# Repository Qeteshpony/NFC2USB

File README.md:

# NFC2USB

[Documentation](https://qeteshpony.github.io/NFC2USB)

Connect an RC522 based NFC-Reader to your computer using USB

The project is based around an [ESP32-S2FH4](https://www.espressif.com/sites/default/files/documentation/esp32-s2_datasheet_en.pdf) with it's most basic support components and no RF circuitry since we just need GPIO and processing power. It would have been possible to solve this with a much simpler microcontroller but availability and pricing at the time of development made the ESP32 with built in USB and flash the best choice. 

The board is designed using KiCAD 6 with production and assembly by JLCPCB in mind. All parts are selected to be available from JLCPCB at the time of writing and as many parts as possible are used from their basic library.

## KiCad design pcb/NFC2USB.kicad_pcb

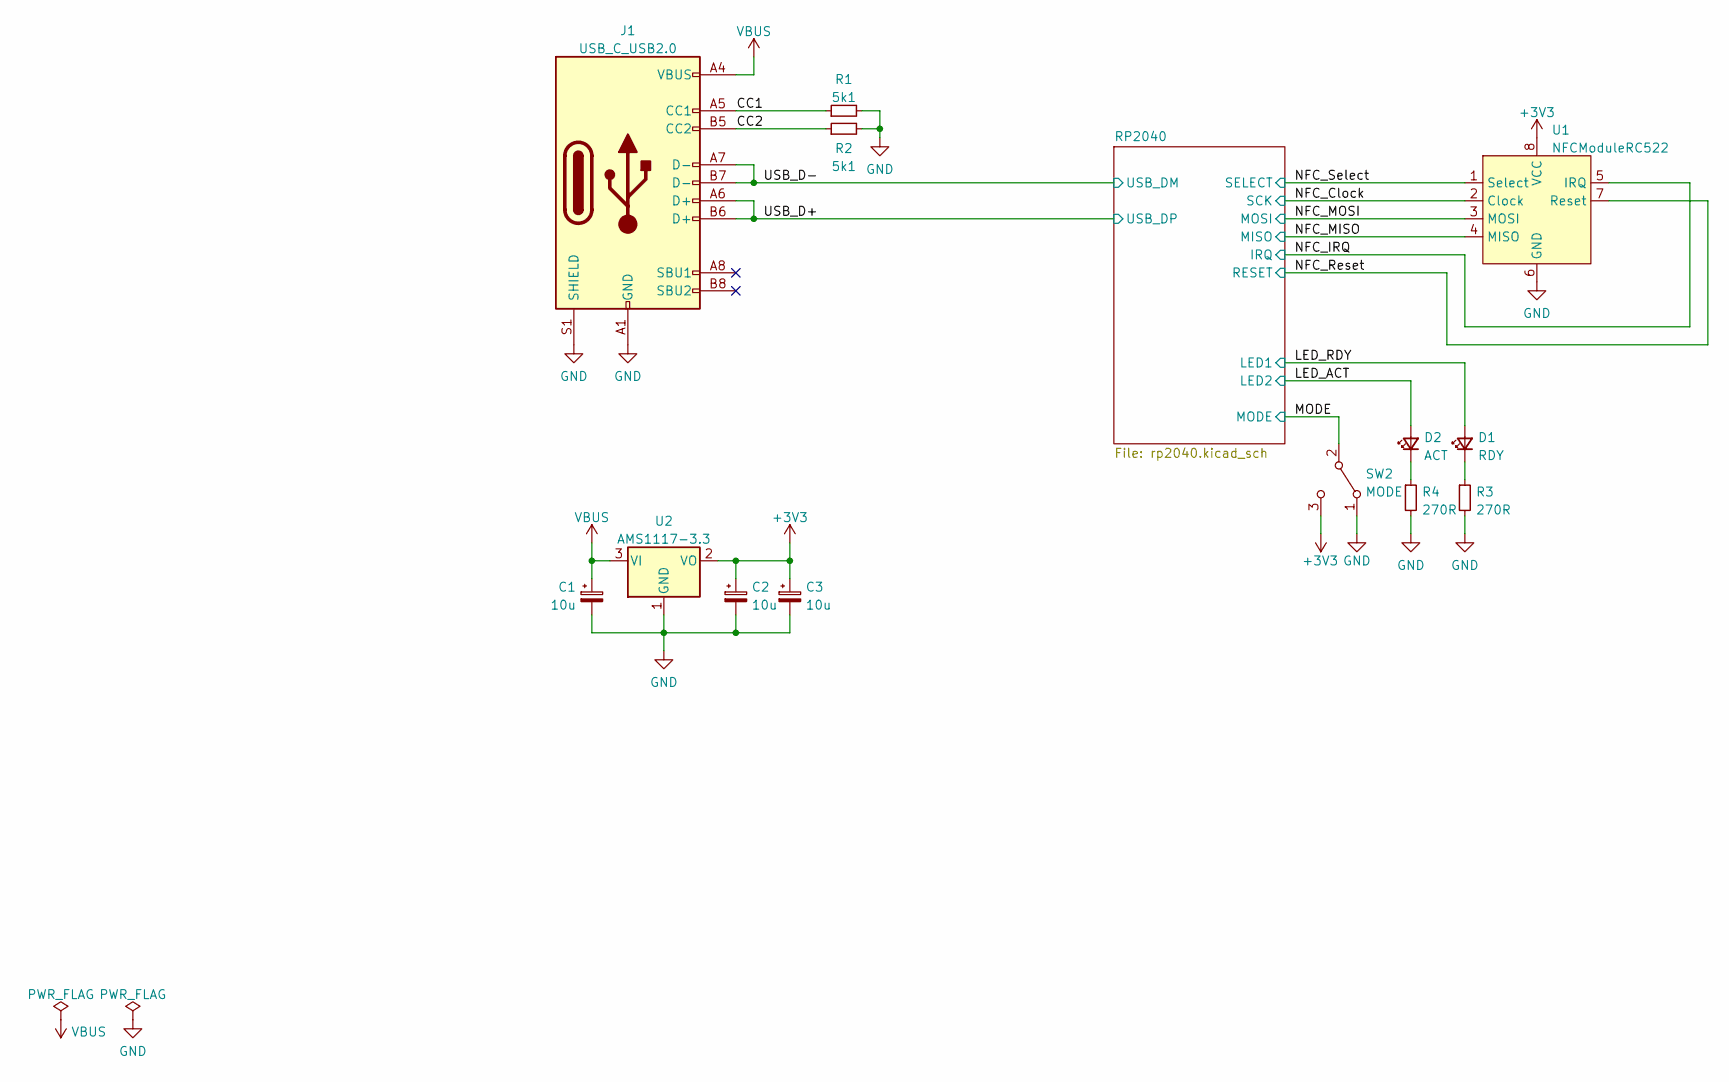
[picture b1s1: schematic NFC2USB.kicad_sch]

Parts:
C1, C2, C3: 10u; CP_EIA-3216-18_Kemet-A; LCSC C7171
D1: RDY; LED_0603_1608Metric; LCSC C72043
D2: ACT; LED_0603_1608Metric; LCSC C72038
J1: USB_C_USB2.0; USB_C_Receptacle_HRO_TYPE-C-31-M-12; LCSC C2894897
R1, R2: 5k1; R_0402_1005Metric; LCSC C25905
R3, R4: 270R; R_0603_1608Metric; LCSC C22966
SW2: MODE; SW_SPDT_PCM12; LCSC C431541
U1: NFCModuleRC522; PinSocket_1x08_P2.54mm_Vertical
U2: AMS1117-3.3; SOT-223-3_TabPin2; LCSC C6186

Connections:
+3V3: C2.1, C3.1, SW2.3 (C), U1.8 (VCC), U2.2 (VO); also elsewhere on the board
/CC1: J1.A5 (CC1), R1.1
/CC2: J1.B5 (CC2), R2.1
/LED_ACT: D2.2 (A); also elsewhere on the board
/LED_RDY: D1.2 (A); also elsewhere on the board
/MODE: SW2.2 (B); also elsewhere on the board
/NFC_Clock: U1.2 (Clock); also elsewhere on the board
/NFC_IRQ: U1.5 (IRQ); also elsewhere on the board
/NFC_MISO: U1.4 (MISO); also elsewhere on the board
/NFC_MOSI: U1.3 (MOSI); also elsewhere on the board
/NFC_Reset: U1.7 (Reset); also elsewhere on the board
/NFC_Select: U1.1 (Select); also elsewhere on the board
/USB_D+: J1.A6 (D+), J1.B6 (D+); also elsewhere on the board
/USB_D-: J1.A7 (D-), J1.B7 (D-); also elsewhere on the board
GND: C1.2, C2.2, C3.2, J1.A1 (GND), J1.A12 (GND), J1.B1 (GND), J1.B12 (GND), J1.S1 (SHIELD), R1.2, R2.2, R3.2, R4.2, SW2.1 (A), U1.6 (GND), U2.1 (GND); also elsewhere on the board
unnamed: D1.1 (K), R3.1
unnamed: D2.1 (K), R4.1
VBUS: C1.1, J1.A4 (VBUS), J1.A9 (VBUS), J1.B4 (VBUS), J1.B9 (VBUS), U2.3 (VI)

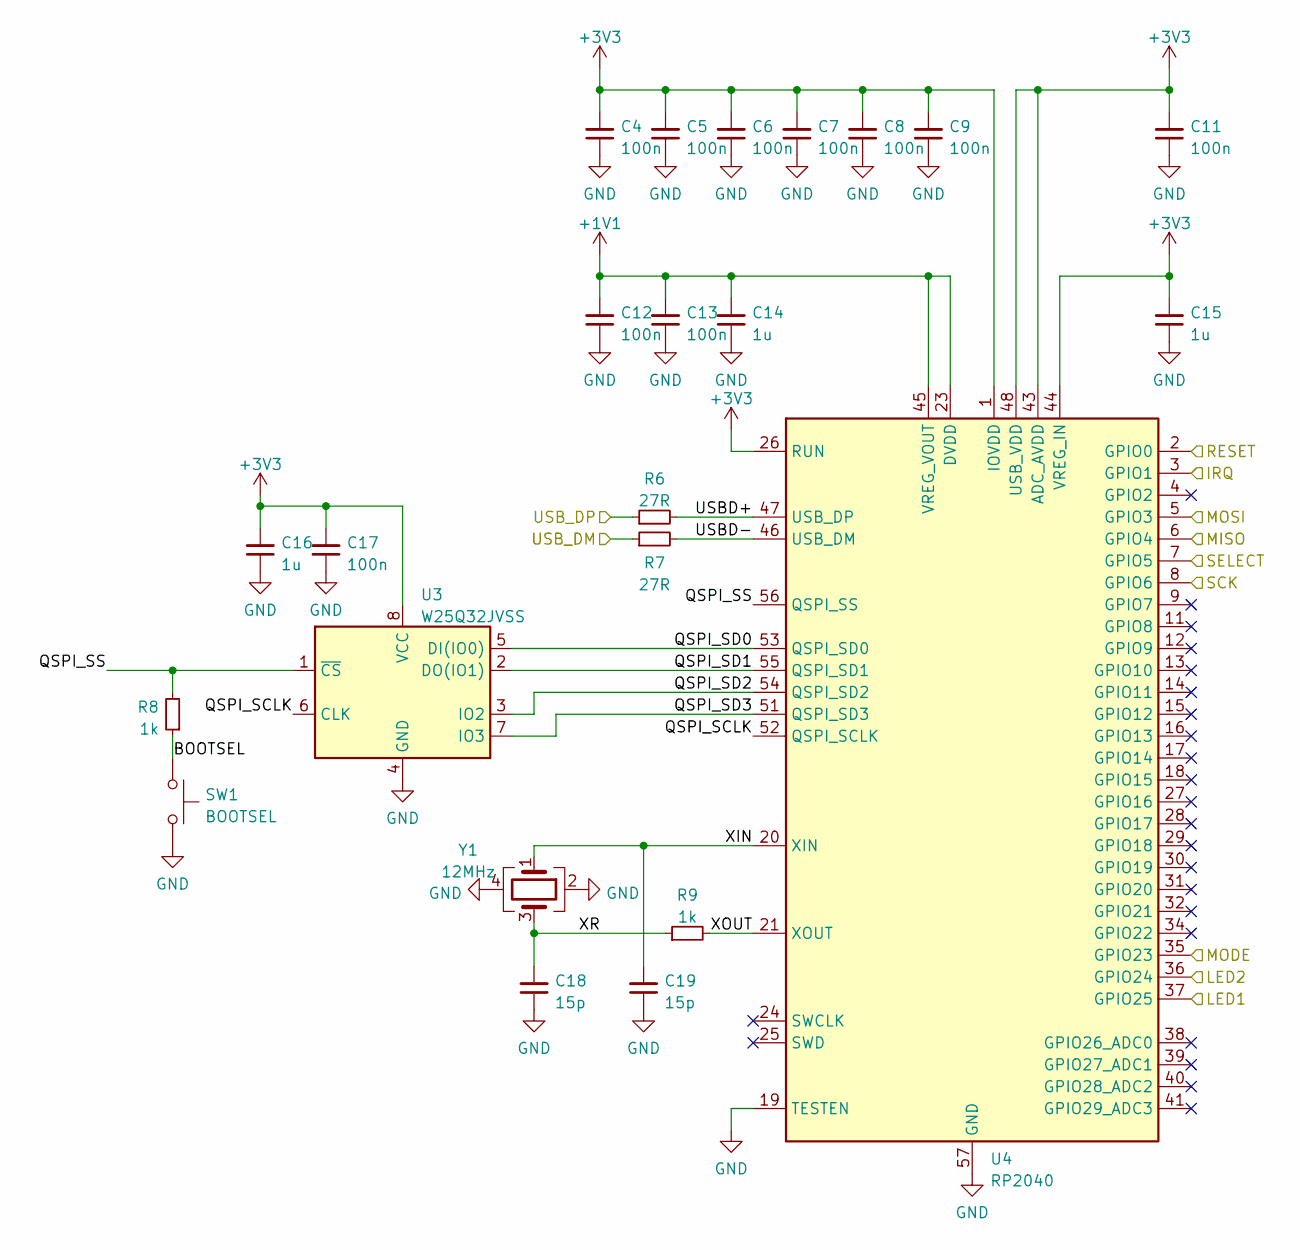
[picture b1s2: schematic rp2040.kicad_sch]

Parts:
C4, C5, C6, C7, C8, C9, C11, C12, C13, C17: 100n; C_0402_1005Metric; LCSC C1525
C14, C15, C16: 1u; C_0402_1005Metric; LCSC C52923
C18, C19: 15p; C_0402_1005Metric; LCSC C1548
R6, R7: 27R; R_0402_1005Metric; LCSC C25100
R8, R9: 1k; R_0402_1005Metric; LCSC C11702
SW1: BOOTSEL; SW_SPST_TL3342; LCSC C318884
U3: W25Q32JVSS; SOIC-8_5.23x5.23mm_P1.27mm; LCSC C179173
U4: RP2040; QFN-56-1EP_7x7mm_P0.4mm_EP3.2x3.2mm; LCSC C2040
Y1: 12MHz; Crystal_SMD_3225-4Pin_3.2x2.5mm; LCSC C9002

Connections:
+1V1: C12.2, C13.2, C14.2, U4.23 (DVDD), U4.45 (VREG_VOUT), U4.50 (DVDD)
+3V3: C4.2, C5.2, C6.2, C7.2, C8.2, C9.2, C11.2, C15.2, C16.2, C17.2, U3.8 (VCC), U4.1 (IOVDD), U4.10 (IOVDD), U4.22 (IOVDD), U4.26 (RUN), U4.33 (IOVDD), U4.42 (IOVDD), U4.43 (ADC_AVDD), U4.44 (VREG_IN), U4.48 (USB_VDD), U4.49 (IOVDD); also elsewhere on the board
/LED_ACT: U4.36 (GPIO24); also elsewhere on the board
/LED_RDY: U4.37 (GPIO25); also elsewhere on the board
/MODE: U4.35 (GPIO23); also elsewhere on the board
/NFC_Clock: U4.8 (GPIO6); also elsewhere on the board
/NFC_IRQ: U4.3 (GPIO1); also elsewhere on the board
/NFC_MISO: U4.6 (GPIO4); also elsewhere on the board
/NFC_MOSI: U4.5 (GPIO3); also elsewhere on the board
/NFC_Reset: U4.2 (GPIO0); also elsewhere on the board
/NFC_Select: U4.7 (GPIO5); also elsewhere on the board
/RP2040/BOOTSEL: R8.1, SW1.1
/RP2040/QSPI_SCLK: U3.6 (CLK), U4.52 (QSPI_SCLK)
/RP2040/QSPI_SD0: U3.5 (DI(IO0)), U4.53 (QSPI_SD0)
/RP2040/QSPI_SD1: U3.2 (DO(IO1)), U4.55 (QSPI_SD1)
/RP2040/QSPI_SD2: U3.3 (IO2), U4.54 (QSPI_SD2)
/RP2040/QSPI_SD3: U3.7 (IO3), U4.51 (QSPI_SD3)
/RP2040/QSPI_SS: R8.2, U3.1 (~CS), U4.56 (QSPI_SS)
/RP2040/USBD+: R6.2, U4.47 (USB_DP)
/RP2040/USBD-: R7.2, U4.46 (USB_DM)
/RP2040/XIN: C19.2, U4.20 (XIN), Y1.1
/RP2040/XOUT: R9.2, U4.21 (XOUT)
/RP2040/XR: C18.2, R9.1, Y1.3
/USB_D+: R6.1; also elsewhere on the board
/USB_D-: R7.1; also elsewhere on the board
GND: C4.1, C5.1, C6.1, C7.1, C8.1, C9.1, C11.1, C12.1, C13.1, C14.1, C15.1, C16.1, C17.1, C18.1, C19.1, SW1.2, U3.4 (GND), U4.19 (TESTEN), U4.57 (GND), Y1.2, Y1.4; also elsewhere on the board

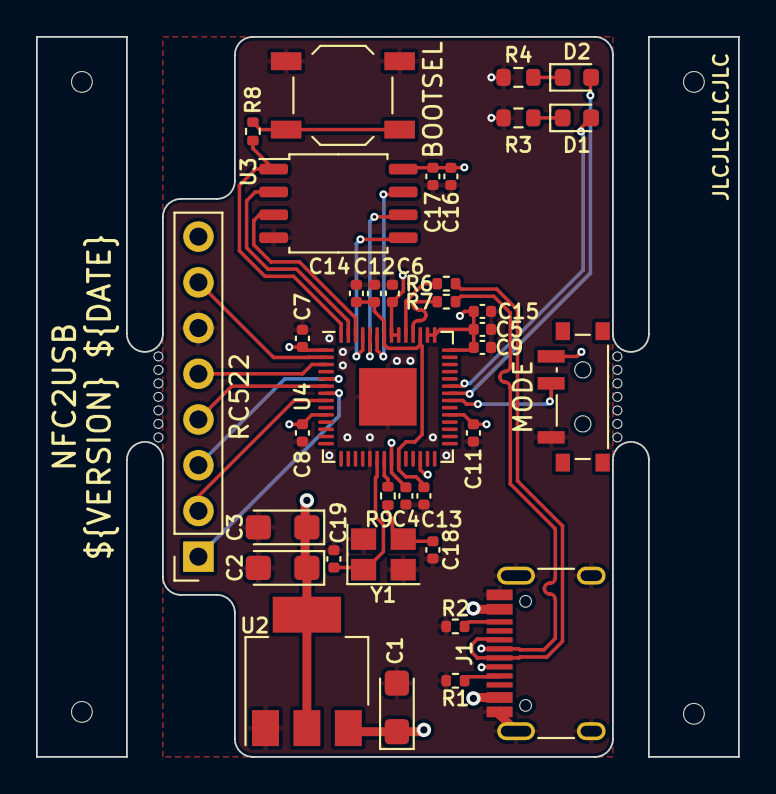
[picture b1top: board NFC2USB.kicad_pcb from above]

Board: 4 copper layers, 39.0 x 40.0 mm, 38 parts (0 on the bottom side), 31 nets.

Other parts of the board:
mouse-bite-2mm-slot, mouse-bite-2mm-slot#2: VAL**; mouse-bite-2x5mm-slot-onesided

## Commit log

2023-03-01 ci: update paths
2023-03-01 ci: trial and error
    trying to fix this mess
2023-03-01 fix: add PWR_FLAGs
2023-03-01 chore: update reference for power nets
2023-03-01 style: (re)move overlapping silkscreen objects
2023-03-01 style: remove more overlapping silkscreen
2023-03-01 docs: add documentation links to README
2023-03-01 ci: change 3d render settings
2023-03-01 style: hide pin sockets from 3d-render
2023-03-01 ci: change 3d render settings (again)
    trial and error...
2023-03-04 feat: change from ESP32 to RP2040
    Changing the Microcontroller to RP2040 because of price, availability and ease of use
2023-03-04 chore(main): release 1.0.0
2023-03-04 style: wrong 3d-model
2023-03-04 style: 3d-model rotation
2023-03-05 docs: update README
2023-03-05 ci: move reusable workflows to own repo
2023-03-05 ci: fix workflow links
2023-03-05 style: board cleanup
2023-03-05 ci: fix link
